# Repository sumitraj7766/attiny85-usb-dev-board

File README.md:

# ATtiny85 USB Development Board

Custom-designed USB-powered ATtiny85 development board created using KiCad.

This project demonstrates PCB design, schematic creation, USB interfacing, voltage regulation, and embedded hardware development.

---

# Project Overview

The board is based on the ATtiny85 microcontroller and includes:

- USB power input
- 5V voltage regulation
- USB data line protection
- LED status indication
- Compact PCB layout

This project was designed for learning embedded systems and PCB development.

---

# Features

✅ USB Powered  
✅ ATtiny85 Microcontroller  
✅ 5V Voltage Regulation  
✅ USB Protection Circuit  
✅ LED Indicator  
✅ Compact PCB Design  
✅ Designed in KiCad  

---

# Hardware Components

| Component | Description |
|---|---|
| ATtiny85-20P | AVR Microcontroller |
| MC78L05 | 5V Voltage Regulator |
| Micro USB Connector | USB Power/Input |
| Zener Diodes | USB Data Protection |
| Capacitors | Voltage Filtering |
| Resistors | Current Limiting |
| LED | Power Indicator |

---

# Software Used

- KiCad
- Embedded C
- AVR Toolchain

---

# Schematic

---

# PCB Layout

---

# Project Structure

```bash
ATtiny85-USB-PCB/
│
├── README.md
│
├── Images/
│   ├── schematic_usb.png
│   ├── power_block.png
│   ├── full_schematic.png
│   ├── pcb_layout.png
│   └── pcb_editor.png
│
├── PCB/
│   ├── pcb1.kicad_pcb
│   ├── pcb1.kicad_pro
│   ├── pcb1.kicad_prl
│   └── pcb1.kicad_sch
│
└── Gerber/
```

---

# Design Blocks

## USB Block
- USB power input
- USB data communication lines
- Zener diode protection

## Power Block
- 5V voltage regulation using MC78L05
- Power filtering capacitors
- LED power indication

## Microcontroller Block
- ATtiny85 microcontroller
- GPIO connections
- Embedded control section

---

# Learning Outcomes

Through this project I learned:

- PCB Design using KiCad
- Schematic Design
- USB Hardware Basics
- Voltage Regulation
- Embedded System Design
- PCB Component Placement
- Routing Concepts

---

# Future Improvements

- Add USB bootloader
- Improve PCB routing
- Add ISP programming header
- Convert design to SMD version
- Add USB-UART communication

---

# Author

**Sumit Kumar**  
Electrical and Electronics Engineering Student

---

# License

This project is open-source and available under the MIT License.

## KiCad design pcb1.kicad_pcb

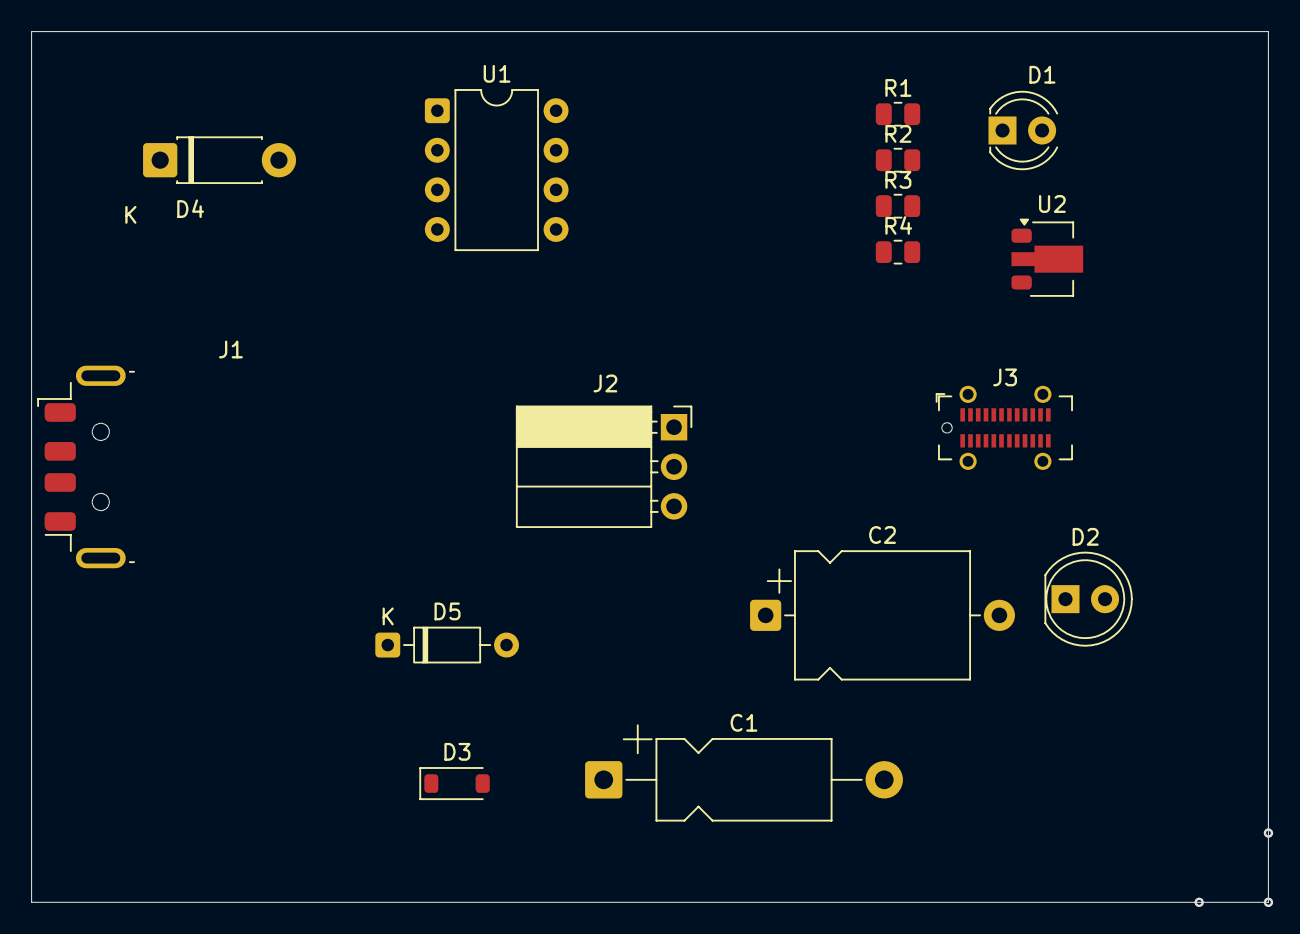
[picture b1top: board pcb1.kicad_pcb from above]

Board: 2 copper layers, 79.4 x 55.9 mm, 16 parts (0 on the bottom side), 12 nets, no tracks yet.

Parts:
C1: C_Small; CP_Axial_L11.0mm_D5.0mm_P18.00mm_Horizontal
C2: C_Small; CP_Axial_L11.0mm_D8.0mm_P15.00mm_Horizontal
D1: LED; LED_D4.0mm
D2: LED; LED_D5.0mm
D3: MBR0520; D_SOD-123
D4: D_Zener; D_DO-41_SOD81_P7.62mm_Horizontal
D5: D_Zener; D_DO-35_SOD27_P7.62mm_Horizontal
J1: I/O; USB_A_Molex_48037-2200_Horizontal
J2: Conn_01x03_Pin; PinSocket_1x03_P2.54mm_Horizontal
J3: USB_B_Micro; USB_C_Receptacle_GCT_USB4115-03-C
R1, R2, R3, R4: R_Small_US; R_0805_2012Metric
U1: ATtiny85-20P; DIP-8_W7.62mm
U2: MC78L05_SOT89; SOT-89-3

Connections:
+5V: C1.1, C2.1, D2.2 (A), D3.2 (A), J2.3, U1.8 (VCC), U2.1 (OUT)
/PB3: J1.3, R3.2, U1.2 (XTAL1/PB3)
/PB4: J1.2, R4.2, U1.3 (XTAL2/PB4)
GND: C1.2, C2.2, D4.1 (K), D5.1 (K), J2.2, R1.2, R2.2, U1.4 (GND), U2.2 (GND)
unnamed: D1.2 (A), U1.6 (PB1)
unnamed: D1.1 (K), R1.1
unnamed: D2.1 (K), R2.1
unnamed: D4.2 (A), R4.1
unnamed: D5.2 (A), R3.1
unnamed: J1.1, U1.1 (~RESET/PB5)
unnamed: J1.4, U1.7 (PB2)
unnamed: J2.1, U2.3 (IN)

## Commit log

2026-05-16 Initial PCB project upload
